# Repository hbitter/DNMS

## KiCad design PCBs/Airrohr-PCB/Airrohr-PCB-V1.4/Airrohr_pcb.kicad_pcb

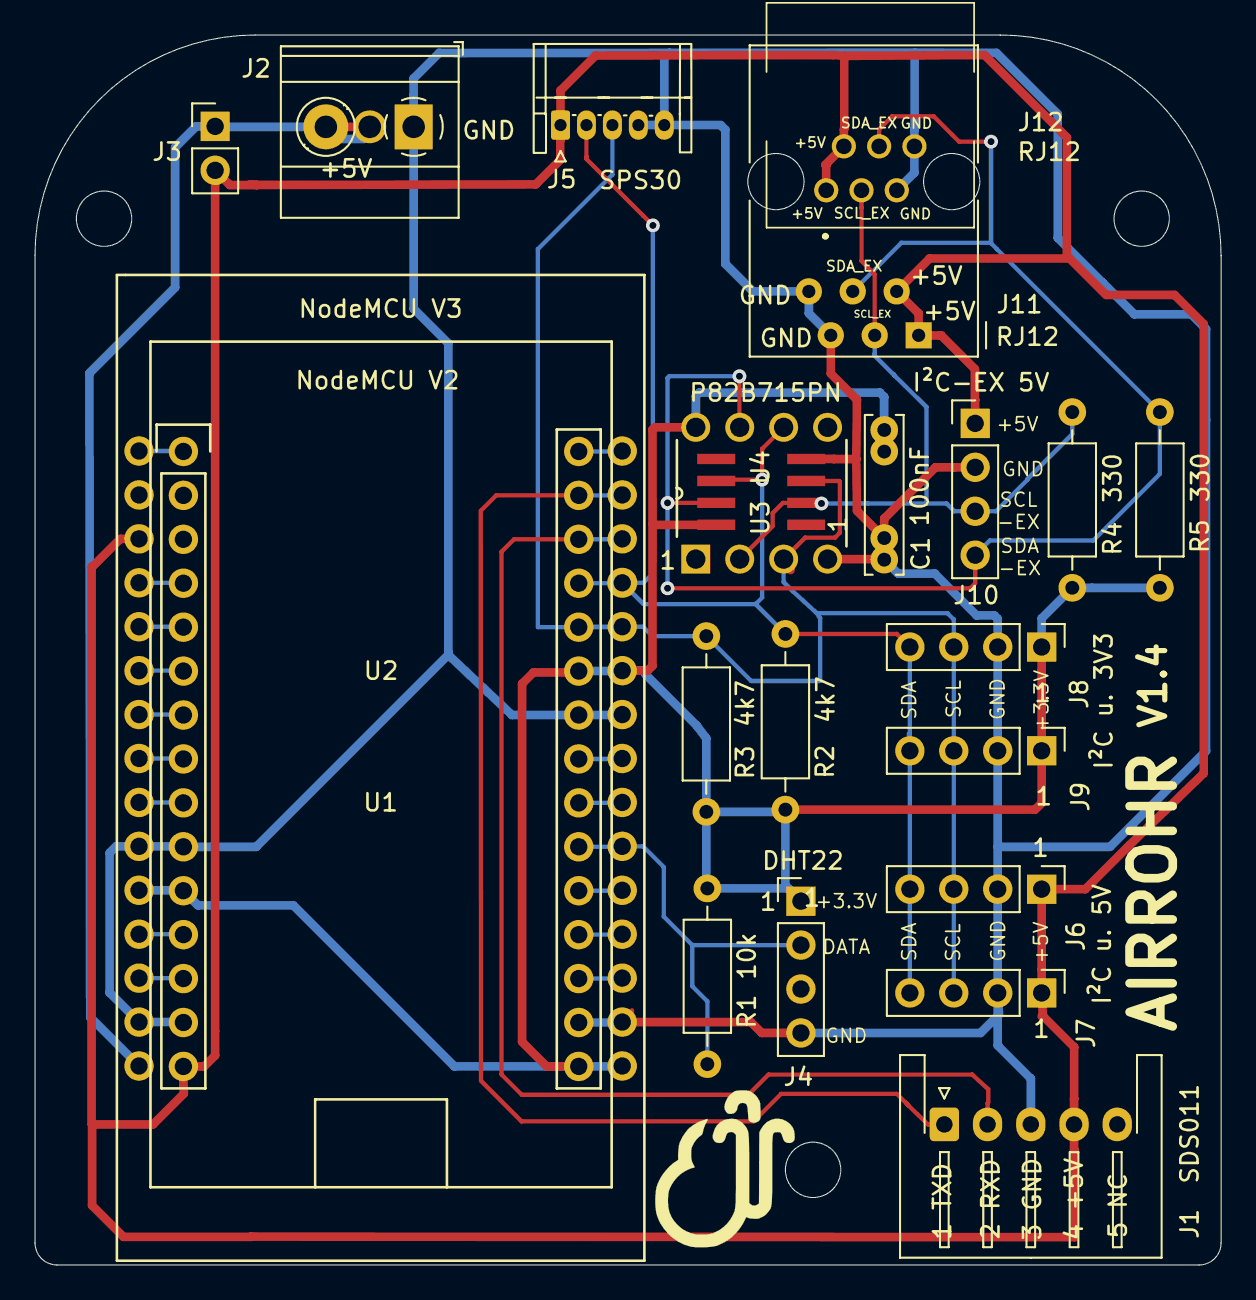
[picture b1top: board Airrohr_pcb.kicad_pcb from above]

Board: 2 copper layers, 68.6 x 71.1 mm, 22 parts (0 on the bottom side), 26 nets.

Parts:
C1: 100nF; C_THT_100nF_L9.0mm_W2.0mm_P5.00mm_P7.50mm
J1: Conn_01x05; JST_XH_S5B-XH-A-1_1x05_P2.50mm_Horizontal
J2: Screw_Terminal_01x02; TerminalBlock_1x02_P2,54mm_P5.08mm_Horizontal
J3: Conn_01x02_Male; PinHeader_1x02_P2.54mm_Vertical
J4, J6, J7, J8, J9, J10: Conn_01x04_Male; PinHeader_1x04_P2.54mm_Vertical
J5: Conn_01x05; JST_ZH_S5B-EH_1x05_P1.50mm_Horizontal
J11: RJ12; RJ12_Amphenol_54601
J12: RJ12; RJ12_Pulse_E5566Q0LK22L
R1: 10k; R_Axial_DIN0207_L6.3mm_D2.5mm_P10.16mm_Horizontal
R2, R3: 4k7; R_Axial_DIN0207_L6.3mm_D2.5mm_P10.16mm_Horizontal
R4, R5: 330; R_Axial_DIN0207_L6.3mm_D2.5mm_P10.16mm_Horizontal
U1: NodeMCU V3; NodeMCU-LoLinV3
U2: NodeMCU V2; NodeMCU_Amica_R2
U3: P82B715PN; DIP254P762X420-8
U4: P82B715DR; SOIC8

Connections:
+3V3: C1.1, J4.1, J8.1, J9.1, R1.1, R2.1, R3.1, R4.1, R5.1, U1.11, U1.16, U1.25, U2.11, U2.16, U2.25, U3.8, U4.8
+5V: J1.4, J3.2, J5.1, J6.1, J7.1, J10.1, J11.1, J11.2, J12.1, J12.2, U1.3, U2.15
GND: C1.2, J1.3, J2.1, J4.4, J5.4, J5.5, J6.2, J7.2, J8.2, J9.2, J10.2, J11.5, J11.6, J12.5, J12.6, U1.10, U1.14, U1.17, U1.24, U2.10, U2.14, U2.17, U2.24, U3.4, U4.4
unnamed: J2.2, J3.1, U1.15
unnamed: J4.2, R1.2, U1.21, U2.21
unnamed: U1.1, U2.1
unnamed: U1.4, U2.4
unnamed: U1.5, U2.5
unnamed: U1.6, U2.6
unnamed: U1.7, U2.7
unnamed: U1.8, U2.8
unnamed: U1.9, U2.9
unnamed: U1.12, U2.12
unnamed: U1.13, U2.13
unnamed: U1.18, U2.18
unnamed: U1.19, U2.19
unnamed: U1.20, U2.20
unnamed: U1.22, U2.22
unnamed: U1.23, U2.23
unnamed: U1.30, U2.30
RXD: J1.2, U1.28, U2.28
SCL: J5.3, J6.3, J7.3, J8.3, J9.3, R3.2, U1.26, U2.26, U3.3, U4.3
SCL-EX: J10.3, J11.3, J12.3, R4.2, U3.2, U4.2
SDA: J5.2, J6.4, J7.4, J8.4, J9.4, R2.2, U1.27, U2.27, U3.6, U4.6
SDA-EX: J10.4, J11.4, J12.4, R5.2, U3.7, U4.7
TXD: J1.1, U1.29, U2.29

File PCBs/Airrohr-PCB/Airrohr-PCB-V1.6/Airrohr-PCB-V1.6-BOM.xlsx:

BOM | Airrohr-PCB-V1.6
Item # | Reference | Qty | Manufacturer | Manufacturer Part # | Description / Value | Package/Footprint | Type | Distributor | Distributor # | Link to Distributor | Link to alternate Source | Link to alternate Source | Notes | Price (single Qty) Mouser | Price
1 | C1 | 1 | Vishay | K104K15X7RF53H5L | Multilayer Ceramic Capacitors MLCC - Leaded 0.1uF 50volts 10% X7R 5mm LS | 5mm LS | THT | Mouser | 594-K104K15X7RF53H5 | Mouser | Reichelt | Voelkner | any other Manufacturer is ok | 0.085 | 0.085
2 | J1 | 1 | JST | S5B-XH-A | Through-hole type shrouded header, siede entry | P2,5mm | THT | Reichelt | JST XH5P ST90 | Reichelt | Voelkner | TME | (optional) | 0.2 | 0.2
3 | J2 | 1 | PTR | 50500020134G | PCB Terminal Block, Screw Terminal, 2-pole | P5,08 | THT | Voelkner | D29644 | Voelkner | Reichelt | Mouser | any other Manufacturer is ok, (optional) | 0.18 | 0.18
4 | J3 | 1 | Amphenol FCI | 10129378-902001BLF | PIN Header 1x02 P2.54mm vertical | P2.54mm | THT | Mouser | 649-1012937890201BLF | Mouser | Reichelt | Voelkner | any other Manufacturer is ok, (optional) | 0.085 | 0.085
5 | J4, J6, J7, J8, J9, J10 | 6 | A+D10:P10mphenol Commercial Products | G800W304018EU | Pin Header 2.54mm Pitch STR DIP,1x4Pin,FULL G/F,NY6T,6.1mm*2.5mm*3.0mm,Color-Bl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 | P2,54mm | THT | Mouser | 523-G800W304018EU | Mouser | Reichelt | Voelkner | any other Manufacturer is ok, (optional) | 0.085 | 0.51
6 | J5 | 1 | JST | S5B-ZR(LF)(SN) | Through-hole type shrouded header, siede entry | P1,5mm | THT | Voelkner | D19571 | Voelkner | smdv |  | (optional) | 0.53 | 0.53
7 | J11 | 1 | Amphenol FCI | 54601-906WPLF | MOD JACK RJ12 6P6C CAT 3 HORIZ. 1 PORT |  | THT | Mouser | 649-54601-906WPLF | Mouser |  |  | either J11 or J12 as alternate assembly, this is the preferred assembly because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 | 0.347 | 0.347
8 | J12 | 1 | Pulse Electronics | E5566-Q0LK22-L | Modular Jack RJ12/RJ25 6P6C SIDE ENTRY |  | THT | Mouser | 673-E5566-Q0LK22-L | Mouser | Reichelt | Voelkner | either J11 or J12 as alternate assembly, any other Manufacturer is ok, (optiona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 | 0.44 | 0.44
9 | R1 | 1 | Vishay | CCF0710K0JKE36 | Metal Film Resistor 1/4watt 10Kohms 5% Rated to 1/2watt | 6,62x2.29mm axial |  | Mouser | 71-CCF0710K0JKE36 | Mouser | Reichelt | Voelkner | any other Manufacturer is ok, Kohleschicht oder Metallschicht, 0,25Watt oder 0,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 | 0.152 | 0.152
10 | R2, R3 | 2 | Vishay | CCF074K70JKE36 | Metal Film Resistor 1/4watt 4.7Kohms 5% Rated to 1/2watt | 6,62x2.29mm axial | THT | Mouser | 71-CCF07-J-4.7K-E3 | Mouser | Reichelt | Voelkner | any other Manufacturer is ok, Kohleschicht oder Metallschicht, 0,25Watt oder 0,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 | 0.152 | 0.304
11 | R4, R5 | 2 | Vishay | CCF07330RJKE36 | Metal Film Resistor 1/4watt 330 Ohms 5% Rated to 1/2watt | 6,62x2.29mm axial |  | Mouser | 71-CCF07330RJKE36 | Mouser | Reichelt | Voelkner | any other Manufacturer is ok, Kohleschicht oder Metallschicht, 0,25Watt oder 0,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 | 0.085 | 0.17
12 | U1 | 1 | diverse | NodeMCU V3 | NodeMCU ESP8266 Entwicklungs Board V3 | 58 x 31mm | THT | KOMPUTER DE | KP06014 | KOMPUTER DE | AZ-Delivery |  | either U1 or U2 as alternate assembly | 3.12 | 3.12
13 | U2 | 1 | diverse | NodeMCU V2 | ESP8266 NodeMCU V2 Delopment Board | 48 x 26mm | THT | AZ-Delivery | NodeMCU Lua Amica Modul V2 ESP8266 ESP-12F | AZ-Delivery | BerryBase |  | either U1 or U2 as alternate assembly | 5.79 | 5.79
14 | U3 | 1 | Texas Instruments | P82B715P | Signal Buffer, Verstärker I2C Bus Extender | DIP8 | THT | Mouser | 595-P82B715P | Mouser |  |  | either U3 or U4 as alternate assembly, any other Manufacturer is ok, (optional) | 2.29 | 2.29
15 | U4 | 1 | Texas Instruments | P82B715DR | Signal Buffer, Verstärker I2C Bus Extender | SOIC8 | SMD | Mouser | 595-P82B715DR | Mouser | Reichelt |  | either U3 or U4 as alternate assembly, any other Manufacturer is ok, (optional) | 1.58 | 1.58

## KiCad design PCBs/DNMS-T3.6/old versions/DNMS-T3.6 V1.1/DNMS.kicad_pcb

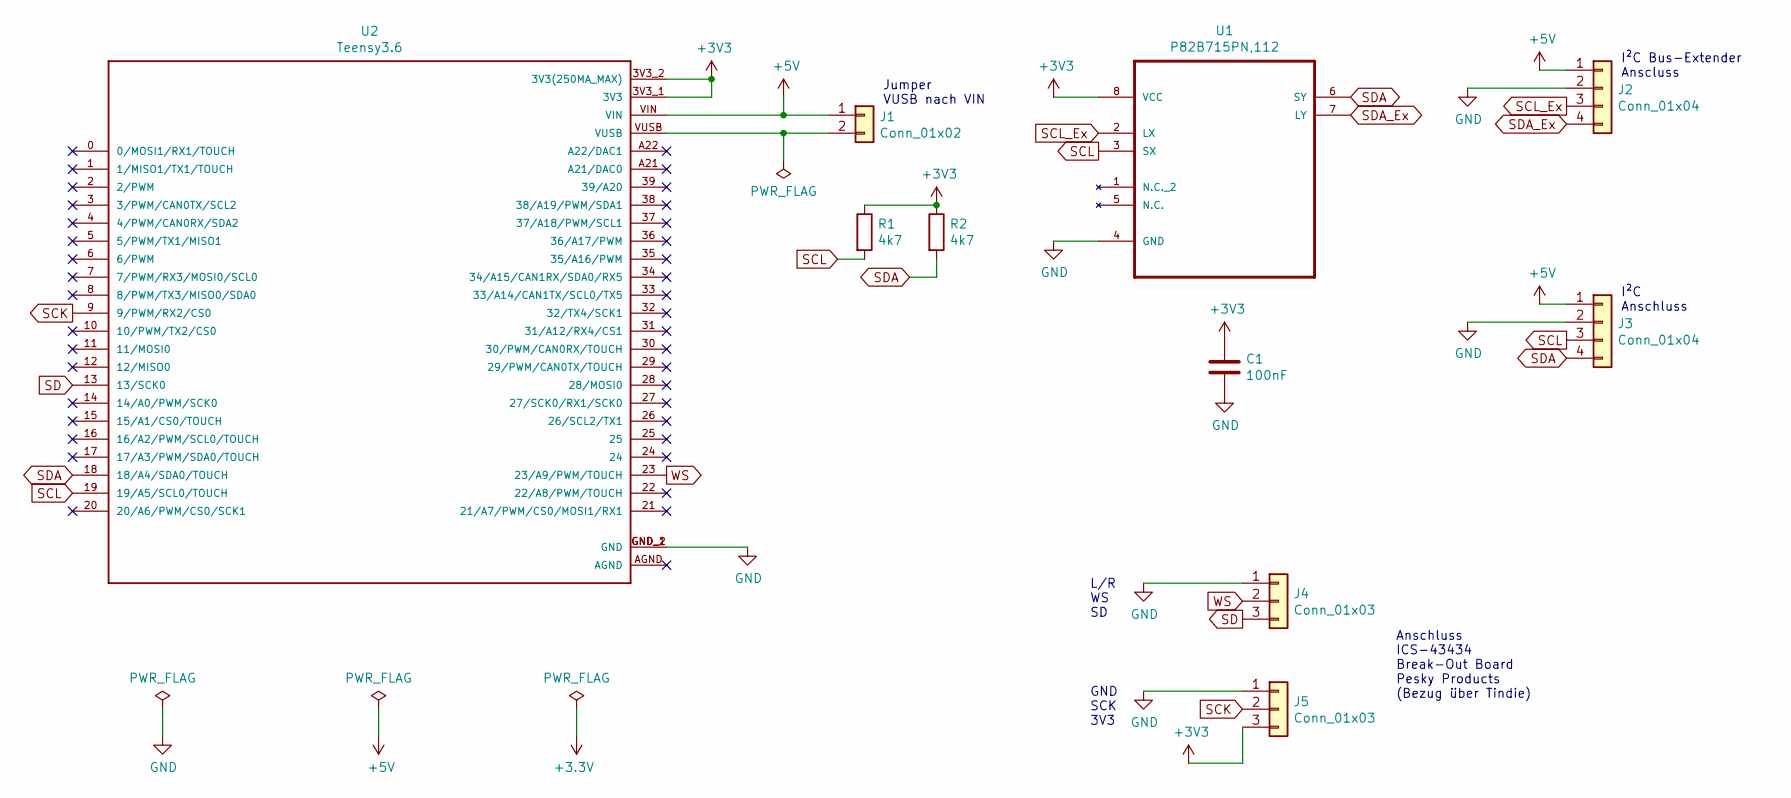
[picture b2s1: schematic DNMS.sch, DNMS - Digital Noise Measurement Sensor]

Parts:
C1: 100nF; C_Axial_L3.8mm_D2.6mm_P7.50mm_Horizontal
J1: Conn_01x02; PinHeader_1x02_P2.54mm_Vertical
J2, J3: Conn_01x04; PinHeader_1x04_P2.54mm_Vertical
J4, J5: Conn_01x03; PinHeader_1x03_P2.54mm_Vertical
R1, R2: 4k7; R_Axial_DIN0207_L6.3mm_D2.5mm_P10.16mm_Horizontal
U1: P82B715PN,112; DIP254P762X420-8
U2: Teensy3.6

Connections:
+3V3: C1.1, J5.3, R1.1, R2.1, U1.8 (VCC), U2.3V3_1 (3V3), U2.3V3_2 (3V3(250MA_MAX))
+5V: J1.1, J2.1, J3.1, U2.VIN
GND: C1.2, J2.2, J3.2, J4.1, J5.1, U1.4 (GND), U2.GND_1 (GND), U2.GND_2 (GND)
unnamed: J1.2, U2.VUSB
SCK: J5.2, U2.9 (9/PWM/RX2/CS0)
SCL: J3.3, R1.2, U1.3 (SX), U2.19 (19/A5/SCL0/TOUCH)
SCL_Ex: J2.3, U1.2 (LX)
SD: J4.3, U2.13 (13/SCK0)
SDA: J3.4, R2.2, U1.6 (SY), U2.18 (18/A4/SDA0/TOUCH)
SDA_Ex: J2.4, U1.7 (LY)
WS: J4.2, U2.23 (23/A9/PWM/TOUCH)

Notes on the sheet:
I²C Bus-Extender Anscluss
I²C Anschluss
Jumper VUSB nach VIN
L/R WS SD
Anschluss ICS-43434 Break-Out Board Pesky Products (Bezug über Tindie)
GND SCK 3V3

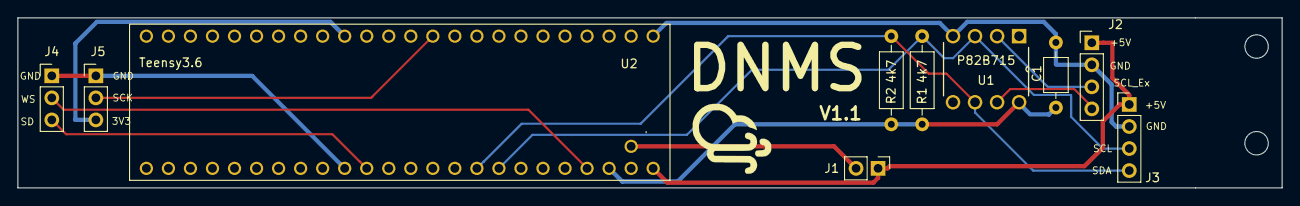
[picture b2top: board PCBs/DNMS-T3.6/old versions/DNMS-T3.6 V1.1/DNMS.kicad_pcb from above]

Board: 2 copper layers, 145.7 x 19.6 mm, 12 parts (0 on the bottom side), 11 nets.

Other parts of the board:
REF1, REF2: MountingHole_2.7mm_M2.5

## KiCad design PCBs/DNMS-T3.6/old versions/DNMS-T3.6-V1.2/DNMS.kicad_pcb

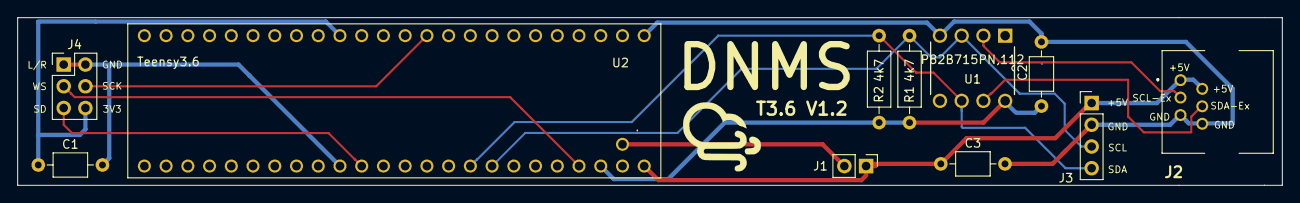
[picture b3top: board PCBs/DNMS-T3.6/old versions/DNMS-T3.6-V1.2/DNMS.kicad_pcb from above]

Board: 2 copper layers, 147.8 x 19.6 mm, 11 parts (0 on the bottom side), 9 nets.

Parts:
C1, C2, C3: 100nF; C_Axial_L3.8mm_D2.6mm_P7.50mm_Horizontal
J1: Conn_01x02; PinHeader_1x02_P2.54mm_Vertical
J2: RJ12; RJ12_Pulse_E5566Q0LK22L
J3: Conn_01x04; PinHeader_1x04_P2.54mm_Vertical
J4: Conn_2Rows-07Pins; PinHeader_2x03_P2.54mm_Vertical
R1, R2: 4k7; R_Axial_DIN0207_L6.3mm_D2.5mm_P10.16mm_Horizontal
U1: P82B715PN,112; DIP254P762X420-8
U2: Teensy3.6

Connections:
+3V3: C1.1, C2.1, J4.6, R1.1, R2.1, U1.8, U2.3V3_1, U2.3V3_2
+5V: C3.1, J1.1, J2.1, J2.2, J3.1, U2.VIN
GND: C1.2, C2.2, C3.2, J2.5, J2.6, J3.2, J4.1, J4.2, U1.4, U2.GND_1, U2.GND_2
unnamed: J1.2, U2.VUSB
SCK: J4.4, U2.9
SCL: J3.3, R1.2, U1.3, U2.19
SD: J4.5, U2.13
SDA: J3.4, R2.2, U1.6, U2.18
WS: J4.3, U2.23
